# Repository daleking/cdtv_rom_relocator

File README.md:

# CDTV Extended ROM and CPU Relocator

I wanted to use a single 27C400 for the extended ROM in my CDTV because 2x
27C1000's are a pain.  A single socket for the rom also makes debugging easier
because I can use a single flashed based rom.  This means I can easily pop in
[CDTV Land's replacement ROM](https://cdtvland.com/os235/) and easily burn or
test future updates.

The second goal was to relocate the CPU socket in such a way to allow an
accelerator such as a TF536 or 020-TK to be installed without interferring with
caps and in such a way that by soldering everything together the case for the
CDTV could still be closed.

Hence the CDTV ROM Relocator was born.  It's a simple relocator with some
decoding logic for the extended ROM and a jumper to disable/enable the rom
(since JP15 on the motherboard only drives logic to the motherboard roms).

By trimming the CPU pins and soldering together a sandwich, the case can be
closed.

If you want to build one you can try the [gerbers from
here](CDTV_Reromlocator/gerbers_v3.zip).

## Photos

This is the bare relocator with an empty 68000 socket.  Installing the original
68000 will still work and the case can still be closed.

**Note!**  If you install a socket for the accelerator you will likely not be able
to close the case.  I recommend soldering the accelerator directly to the
relocator but please do this at your own risk!

Here we have an installed TF536 and CDTV OS 2.35 on a single 27C400.

Case closed!  The tallest component is the ROM, which still has a mm or two
before it touches the case.

We'll need an accelerator.  I like the TF536 with the [firmware from
here](https://www.exxoshost.co.uk/forum/viewtopic.php?f=76&t=3542&sid=06fe9e624b3ed6e35e5968cf34cc0226&start=30#p70123)
which disables the flashy boot rom on the TF536 (that is in the same address
space as the extended ROM).

You will also want a right angled IDE header, not a straight one.  This means
the cable connector is nice and flat.

You will want to solder down and trim the legs of your CPU.  In hindsight I
would raise the CPU of the board by a few mm and just solder the leads short.
There is enough height left for the CPU to sit a little proud but please do
test fit before soldering.

I used regular pin strips between the relocator board and the TF536.  The
plastic at the bottom is the height I chose as a safe distance between the two
PCBs.

Here they are just before soldering together.  Check there is nothing that will
short.  I used a bit of cardboard to keep everything spaced nicely and as a bit
of extra protection in case the boards got smooshed by the case.

Testing installed height.  In my case the ROM is the tallest component.  You
could try and find a lower profile DIP socket for the ROM.

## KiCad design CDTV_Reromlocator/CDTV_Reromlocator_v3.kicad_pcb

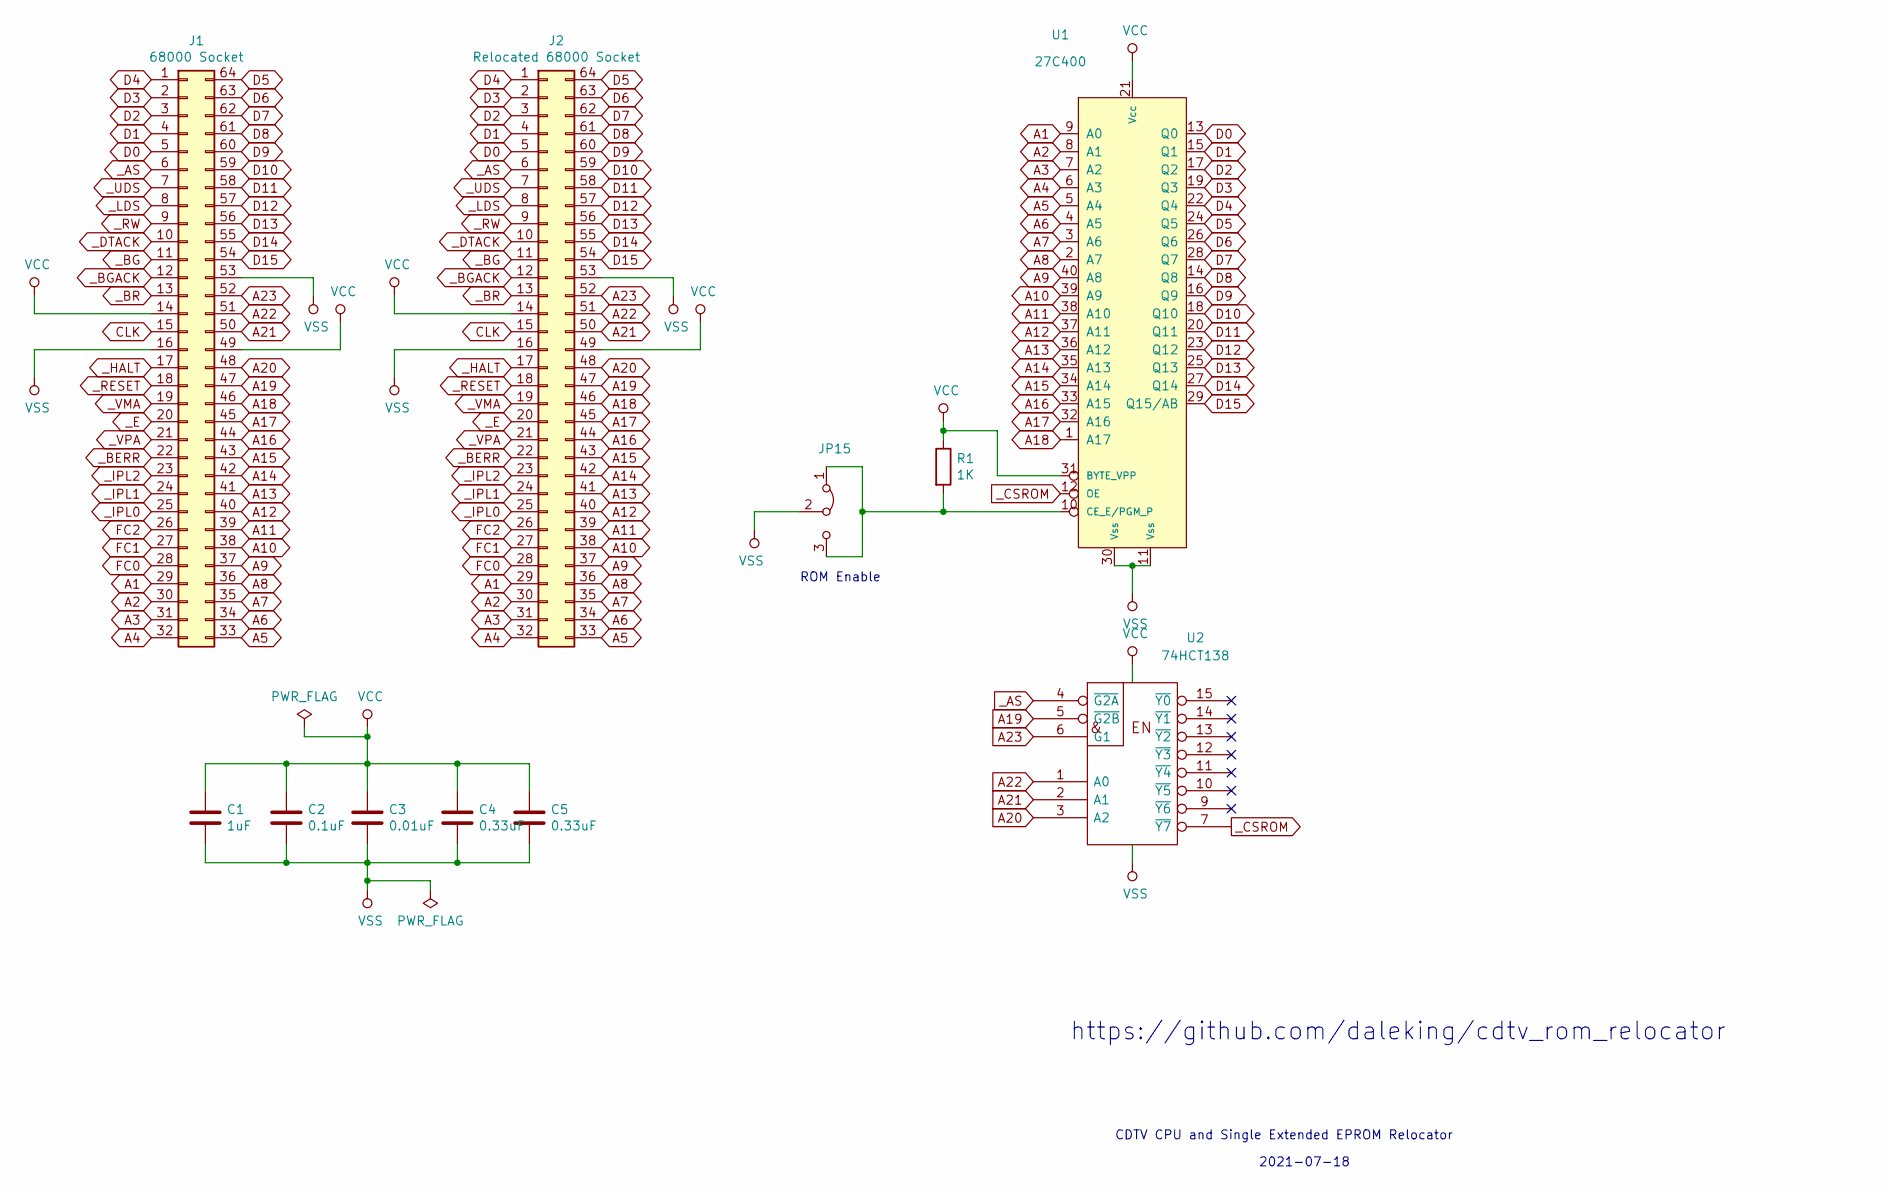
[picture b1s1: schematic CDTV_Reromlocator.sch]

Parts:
C1: 1uF; C_1206_3216Metric_Pad1.42x1.75mm_HandSolder
C2: 0.1uF; C_0805_2012Metric_Pad1.15x1.40mm_HandSolder
C3: 0.01uF; C_0805_2012Metric_Pad1.15x1.40mm_HandSolder
C4, C5: 0.33uF; C_1206_3216Metric_Pad1.42x1.75mm_HandSolder
J1: 68000 Socket; DIP-64_W22.86mm_Socket
J2: Relocated 68000 Socket; DIP-64_W22.86mm_Socket
JP15: Jumper_3_Bridged12; PinHeader_1x03_P2.54mm_Vertical
R1: 1K; R_1206_3216Metric_Pad1.42x1.75mm_HandSolder
U1: 27C400; DIP-40_W15.24mm_Socket
U2: 74HCT138; SOIC-16_3.9x9.9mm_P1.27mm

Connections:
A1: J1.29, J2.29, U1.9 (A0)
A2: J1.30, J2.30, U1.8 (A1)
A3: J1.31, J2.31, U1.7 (A2)
A4: J1.32, J2.32, U1.6 (A3)
A5: J1.33, J2.33, U1.5 (A4)
A6: J1.34, J2.34, U1.4 (A5)
A7: J1.35, J2.35, U1.3 (A6)
A8: J1.36, J2.36, U1.2 (A7)
A9: J1.37, J2.37, U1.40 (A8)
A10: J1.38, J2.38, U1.39 (A9)
A11: J1.39, J2.39, U1.38 (A10)
A12: J1.40, J2.40, U1.37 (A11)
A13: J1.41, J2.41, U1.36 (A12)
A14: J1.42, J2.42, U1.35 (A13)
A15: J1.43, J2.43, U1.34 (A14)
A16: J1.44, J2.44, U1.33 (A15)
A17: J1.45, J2.45, U1.32 (A16)
A18: J1.46, J2.46, U1.1 (A17)
A19: J1.47, J2.47, U2.5 (~G2B)
A20: J1.48, J2.48, U2.3 (A2)
A21: J1.50, J2.50, U2.2 (A1)
A22: J1.51, J2.51, U2.1 (A0)
A23: J1.52, J2.52, U2.6 (G1)
CLK: J1.15, J2.15
D0: J1.5, J2.5, U1.13 (Q0)
D1: J1.4, J2.4, U1.15 (Q1)
D2: J1.3, J2.3, U1.17 (Q2)
D3: J1.2, J2.2, U1.19 (Q3)
D4: J1.1, J2.1, U1.22 (Q4)
D5: J1.64, J2.64, U1.24 (Q5)
D6: J1.63, J2.63, U1.26 (Q6)
D7: J1.62, J2.62, U1.28 (Q7)
D8: J1.61, J2.61, U1.14 (Q8)
D9: J1.60, J2.60, U1.16 (Q9)
D10: J1.59, J2.59, U1.18 (Q10)
D11: J1.58, J2.58, U1.20 (Q11)
D12: J1.57, J2.57, U1.23 (Q12)
D13: J1.56, J2.56, U1.25 (Q13)
D14: J1.55, J2.55, U1.27 (Q14)
D15: J1.54, J2.54, U1.29 (Q15/AB)
FC0: J1.28, J2.28
FC1: J1.27, J2.27
FC2: J1.26, J2.26
GND: C1.2, C2.2, C3.2, C4.2, C5.2, J1.16, J1.53, J2.16, J2.53, JP15.2 (C), U1.11 (Vss), U1.30 (Vss), U2.8 (GND)
unnamed: JP15.1 (A), JP15.3 (B), R1.2, U1.10 (CE_E/PGM_P)
VCC: C1.1, C2.1, C3.1, C4.1, C5.1, J1.14, J1.49, J2.14, J2.49, R1.1, U1.21 (Vcc), U1.31 (BYTE_VPP), U2.16 (VCC)
_AS: J1.6, J2.6, U2.4 (~G2A)
_BERR: J1.22, J2.22
_BG: J1.11, J2.11
_BGACK: J1.12, J2.12
_BR: J1.13, J2.13
_CSROM: U1.12 (OE), U2.7 (~Y7)
_DTACK: J1.10, J2.10
_E: J1.20, J2.20
_HALT: J1.17, J2.17
_IPL0: J1.25, J2.25
_IPL1: J1.24, J2.24
_IPL2: J1.23, J2.23
_LDS: J1.8, J2.8
_RESET: J1.18, J2.18
_RW: J1.9, J2.9
_UDS: J1.7, J2.7
_VMA: J1.19, J2.19
_VPA: J1.21, J2.21

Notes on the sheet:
CDTV CPU and Single Extended EPROM Relocator
2021-07-18
https://github.com/daleking/cdtv_rom_relocator
ROM Enable

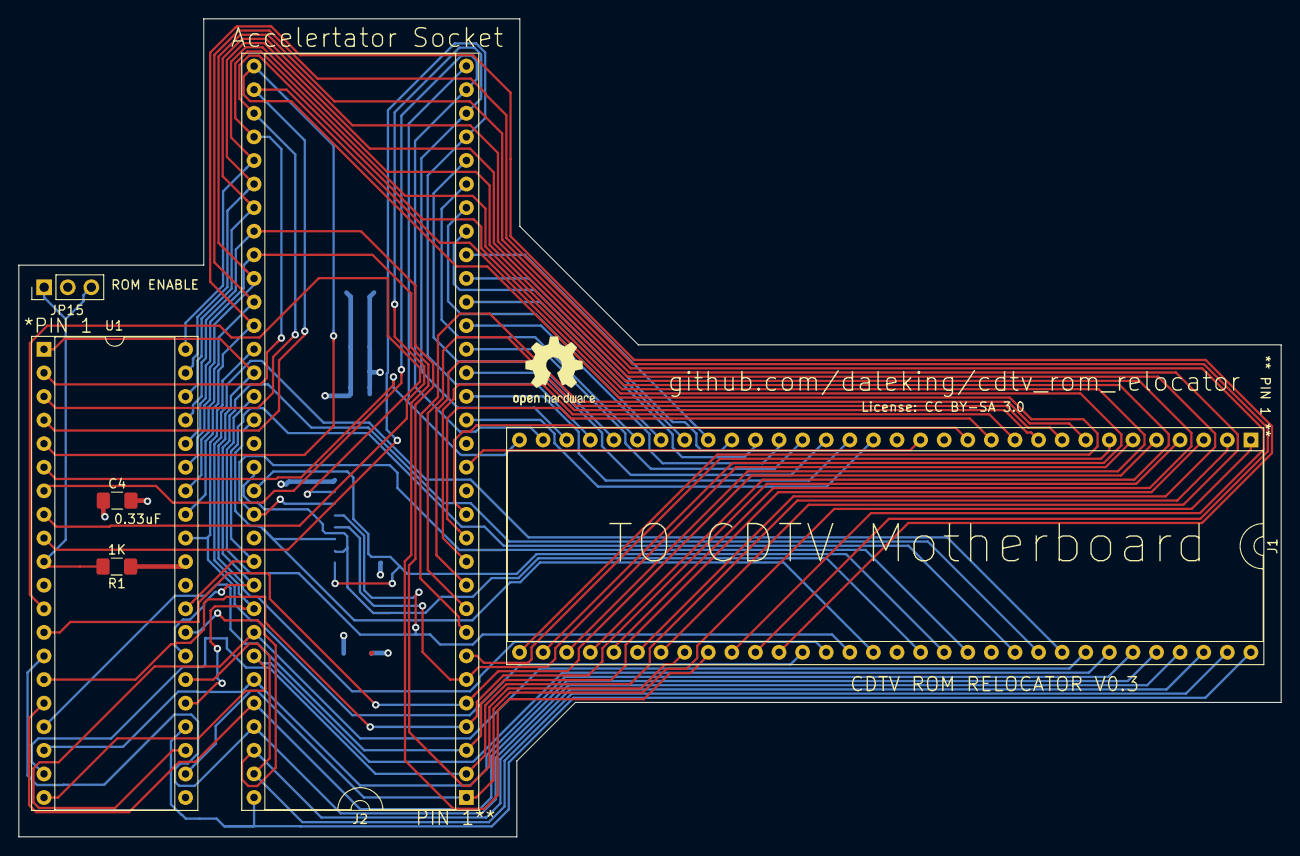
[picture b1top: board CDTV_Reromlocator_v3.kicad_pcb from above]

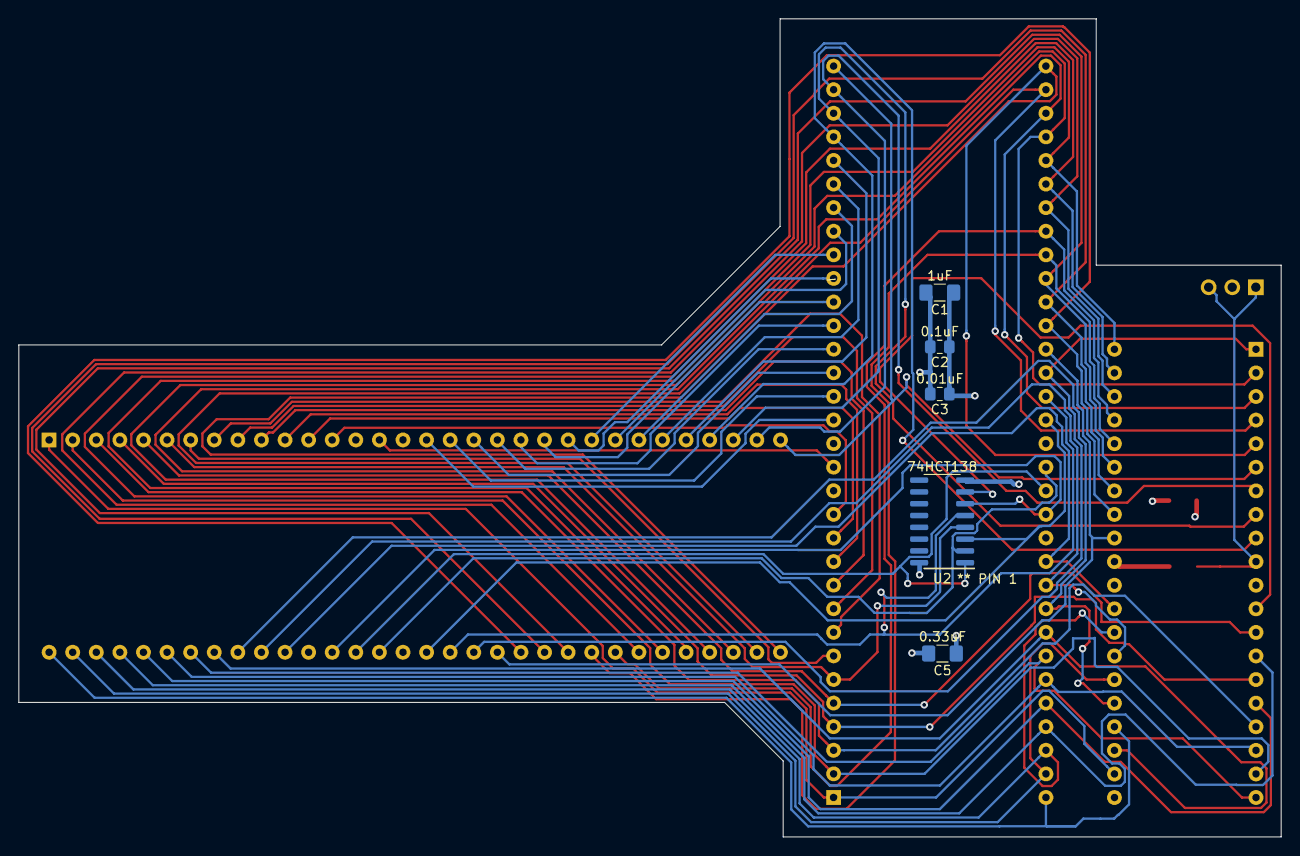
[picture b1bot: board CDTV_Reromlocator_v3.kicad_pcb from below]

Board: 4 copper layers, 135.9 x 88.1 mm, 11 parts (5 on the bottom side), 64 nets.

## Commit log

2022-01-04 initial checkin
2022-01-04 add .csv

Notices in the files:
CDTV_Reromlocator/CDTV_Reromlocator_v3.kicad_pcb:
License: CC BY-SA 3.0
